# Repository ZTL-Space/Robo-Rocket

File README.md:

# Tag der offenen Space Tür - Robo-Rocket-Badge

Das Robo-Rocket-Badge ist ein einfaches Löt-Kit,
dass als Halsband getragen werden kann.

Zum Löten benötigst du einen einfachen Lötkolben,
etwas Lötzinn, eine Abisolierzange und einen Seitenschneider.

### Material

* Robo-Rocket-Platine
* 2 Widerstände, 5,6 Ohm
* 2 LEDs (Blau oder Farbwechsel langsam oder Farbwechsel schnell)
* 2 Leitungen, ca 40cm (schwarz und rot)
* Batteriehalter
* Batterie, CR2032

### Anleitung

Schau dir am besten vorher die Beispiel-Badges auf dem Tisch an.
Damit ist die Erklärung vermutlich viel einfacher zu
lesen.

* Die rote und die schwarze Leitung auf beiden Seiten mit der Abisolierzange abisolieren.

* Alle vier abisolierten Stellen mit Lötzinn verzinnen.

* Anlöten der Leitungen. Dazu die beiden Pads mit ``(+)`` und ``(-)`` an der Spitz der Rakete verzinnen und die rote Leitung an ``(+)`` und die schwarze Leitung an ``(-)`` anlöten.

* Verlöte die LEDs an den Markierungen ``D101`` und ``D102``. Das längere Beinchen muss auf das ``(+)`` Pad.

* Die LEDs knapp über dem Pad um 90° nach oben biegen. Am besten mit dem Finger auf beide Pads drücken, damit diese beim Umbiegen der LED nicht abreißen können.

* Dann die Led-Köpfe wieder nach unten biegen, in Richtung Roboter-Kopf.

* Die Beinchen der beiden Widerstände einkürzen und an den Markierungen ``R101`` und ``R102`` anlöten.

* Zuletzt die beiden Leitungen am Batteriehalter festlöten, die Knopfzelle einsetzen und mit dem Schalter einschalten.

Besonderer Dank geht an chrissi^ (https://gitli.stratum0.org/chrissi/clt-soldering), der das Badge ursprünglich entwickelt hat.

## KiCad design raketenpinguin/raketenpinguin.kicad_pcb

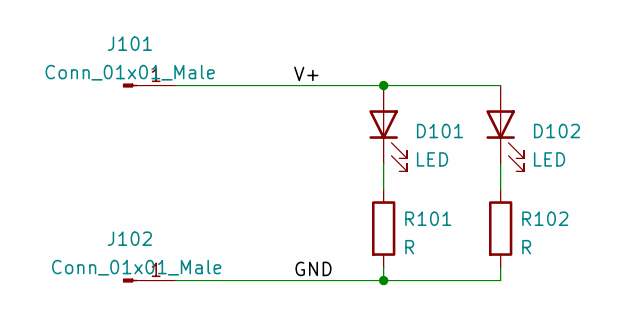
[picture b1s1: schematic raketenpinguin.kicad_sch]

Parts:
D101, D102: LED; led
J101, J102: Conn_01x01_Male; pad
R101, R102: R; res

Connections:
/GND: J102.1, R101.2, R102.2
/V+: D101.2 (A), D102.2 (A), J101.1
unnamed: D101.1 (K), R101.1
unnamed: D102.1 (K), R102.1

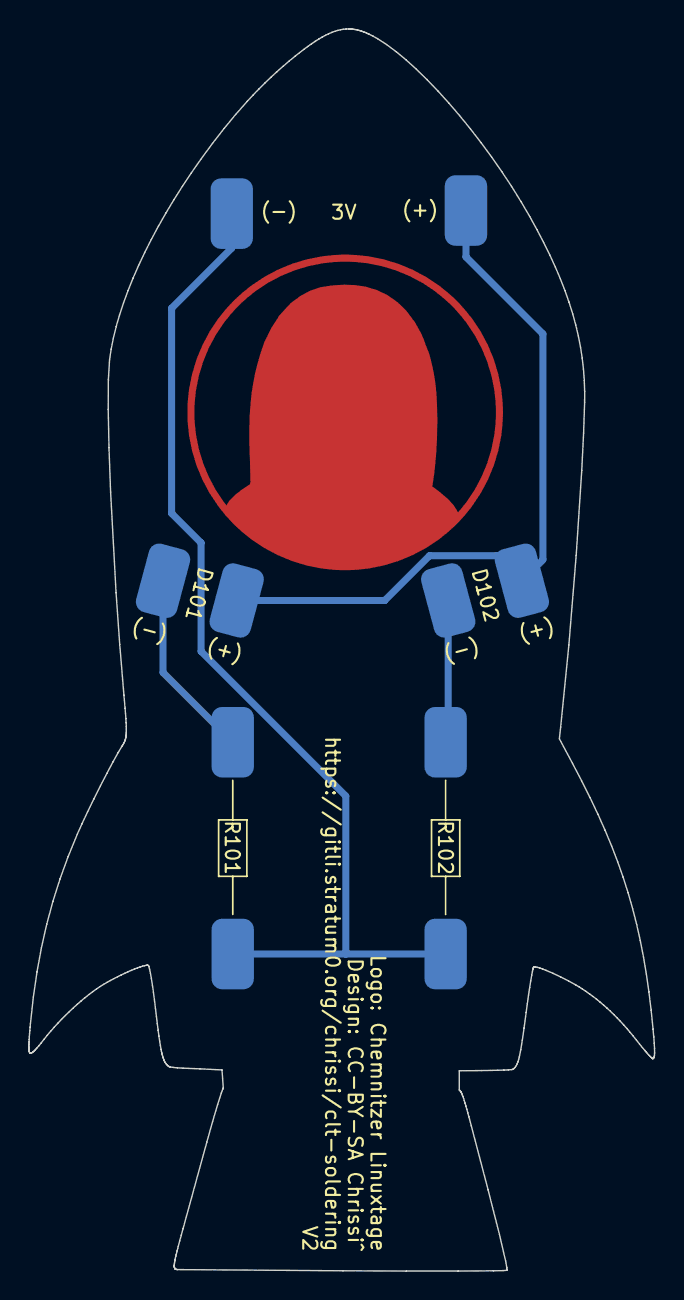
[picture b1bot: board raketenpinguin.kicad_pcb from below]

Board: 2 copper layers, 44.3 x 88.0 mm, 6 parts (6 on the bottom side), 4 nets.

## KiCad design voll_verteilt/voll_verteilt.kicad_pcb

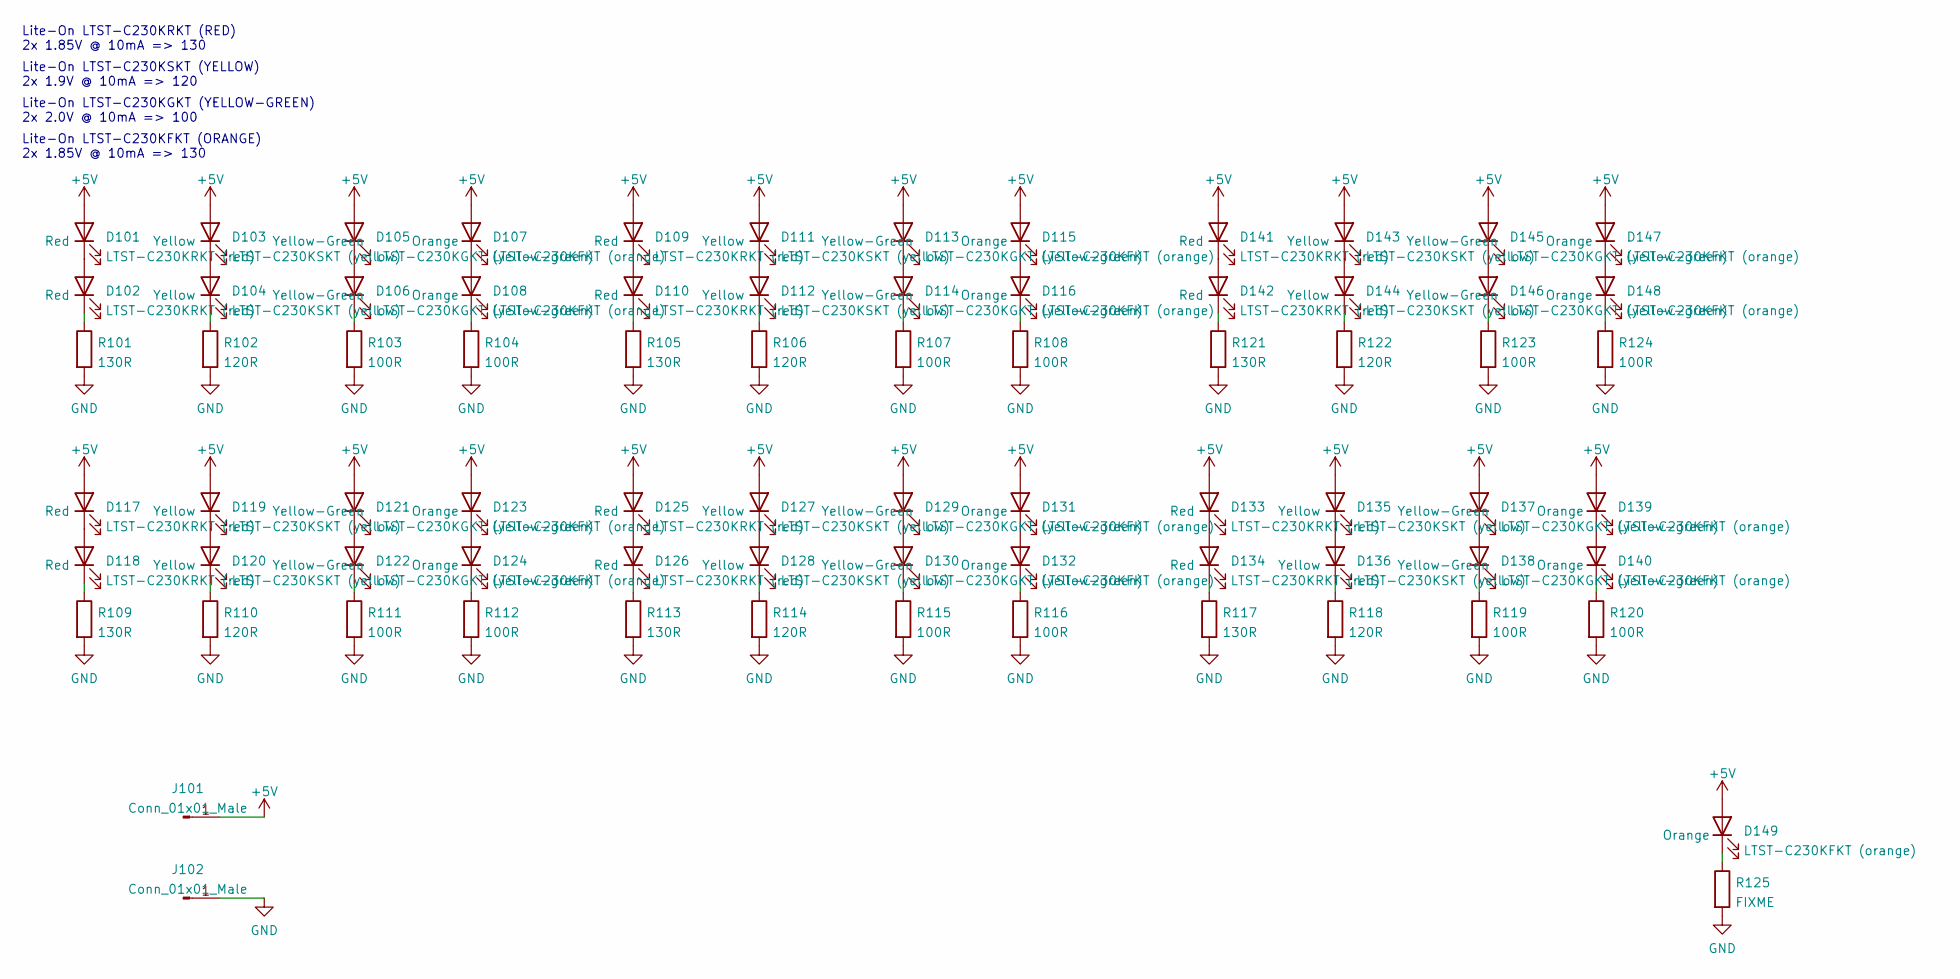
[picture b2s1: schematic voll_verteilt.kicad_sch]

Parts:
D101, D102, D109, D110, D117, D118, D125, D126, D133, D134, D141, D142: LTST-C230KRKT (red); led_counterpost_1206; LCSC# C125107
D103, D104, D111, D112, D119, D120, D127, D128, D135, D136, D143, D144: LTST-C230KSKT (yellow); led_counterpost_1206; LCSC# C125108
D105, D106, D113, D114, D121, D122, D129, D130, D137, D138, D145, D146: LTST-C230KGKT (yellow-green); led_counterpost_1206; LCSC# C125106
D107, D108, D115, D116, D123, D124, D131, D132, D139, D140, D147, D148, D149: LTST-C230KFKT (orange); led_counterpost_1206; LCSC# C284942
J101, J102: Conn_01x01_Male; pad
R101, R105, R109, R113, R117, R121: 130R; R_0603_1608Metric
R102, R106, R110, R114, R118, R122: 120R; R_0603_1608Metric
R103, R104, R107, R108, R111, R112, R115, R116, R119, R120, R123, R124: 100R; R_0603_1608Metric
R125: FIXME; R_0603_1608Metric

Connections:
+5V: D101.2 (A), D103.2 (A), D105.2 (A), D107.2 (A), D109.2 (A), D111.2 (A), D113.2 (A), D115.2 (A), D117.2 (A), D119.2 (A), D121.2 (A), D123.2 (A), D125.2 (A), D127.2 (A), D129.2 (A), D131.2 (A), D133.2 (A), D135.2 (A), D137.2 (A), D139.2 (A), D141.2 (A), D143.2 (A), D145.2 (A), D147.2 (A), D149.2 (A), J101.1
GND: J102.1, R101.2, R102.2, R103.2, R104.2, R105.2, R106.2, R107.2, R108.2, R109.2, R110.2, R111.2, R112.2, R113.2, R114.2, R115.2, R116.2, R117.2, R118.2, R119.2, R120.2, R121.2, R122.2, R123.2, R124.2, R125.2
unnamed: D101.1 (K), D102.2 (A)
unnamed: D102.1 (K), R101.1
unnamed: D103.1 (K), D104.2 (A)
unnamed: D104.1 (K), R102.1
unnamed: D105.1 (K), D106.2 (A)
unnamed: D106.1 (K), R103.1
unnamed: D107.1 (K), D108.2 (A)
unnamed: D108.1 (K), R104.1
unnamed: D109.1 (K), D110.2 (A)
unnamed: D110.1 (K), R105.1
unnamed: D111.1 (K), D112.2 (A)
unnamed: D112.1 (K), R106.1
unnamed: D113.1 (K), D114.2 (A)
unnamed: D114.1 (K), R107.1
unnamed: D115.1 (K), D116.2 (A)
unnamed: D116.1 (K), R108.1
unnamed: D117.1 (K), D118.2 (A)
unnamed: D118.1 (K), R109.1
unnamed: D119.1 (K), D120.2 (A)
unnamed: D120.1 (K), R110.1
unnamed: D121.1 (K), D122.2 (A)
unnamed: D122.1 (K), R111.1
unnamed: D123.1 (K), D124.2 (A)
unnamed: D124.1 (K), R112.1
unnamed: D125.1 (K), D126.2 (A)
unnamed: D126.1 (K), R113.1
unnamed: D127.1 (K), D128.2 (A)
unnamed: D128.1 (K), R114.1
unnamed: D129.1 (K), D130.2 (A)
unnamed: D130.1 (K), R115.1
unnamed: D131.1 (K), D132.2 (A)
unnamed: D132.1 (K), R116.1
unnamed: D133.1 (K), D134.2 (A)
unnamed: D134.1 (K), R117.1
unnamed: D135.1 (K), D136.2 (A)
unnamed: D136.1 (K), R118.1
unnamed: D137.1 (K), D138.2 (A)
unnamed: D138.1 (K), R119.1
unnamed: D139.1 (K), D140.2 (A)
unnamed: D140.1 (K), R120.1
unnamed: D141.1 (K), D142.2 (A)
unnamed: D142.1 (K), R121.1
unnamed: D143.1 (K), D144.2 (A)
unnamed: D144.1 (K), R122.1
unnamed: D145.1 (K), D146.2 (A)
unnamed: D146.1 (K), R123.1
unnamed: D147.1 (K), D148.2 (A)
unnamed: D148.1 (K), R124.1
unnamed: D149.1 (K), R125.1

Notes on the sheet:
Lite-On LTST-C230KGKT (YELLOW-GREEN) 2x 2.0V @ 10mA => 100
Lite-On LTST-C230KSKT (YELLOW) 2x 1.9V @ 10mA => 120
Lite-On LTST-C230KRKT (RED) 2x 1.85V @ 10mA => 130
Lite-On LTST-C230KFKT (ORANGE) 2x 1.85V @ 10mA => 130

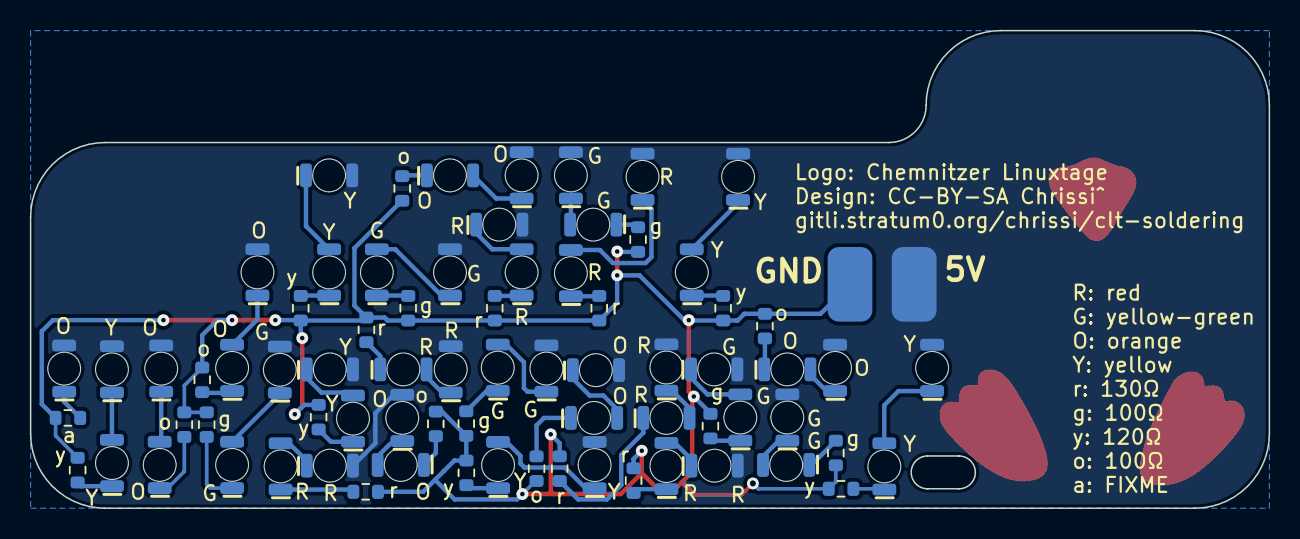
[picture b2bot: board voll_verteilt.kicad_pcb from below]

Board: 2 copper layers, 83.0 x 32.0 mm, 76 parts (76 on the bottom side), 51 nets.

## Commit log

2022-03-01 Raketenpinguin: Add Cu behind head
2022-03-12 Add README
2022-06-12 change raketenpinguin to robo-rocket
2022-06-12 add Gerbers
2022-07-09 add picures and change readme
2022-07-09 text correction
2022-07-09 correction resistor text

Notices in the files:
raketenpinguin/raketenpinguin.kicad_pcb:
Design: CC-BY-SA Chrissi^
